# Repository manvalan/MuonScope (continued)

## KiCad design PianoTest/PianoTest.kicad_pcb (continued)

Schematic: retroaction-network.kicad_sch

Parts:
C201, C232: 1pF C0G; C_0603_1608Metric
C231: 0.5pF C0G; C_0603_1608Metric
C233: 2.2pF C0G; C_0603_1608Metric
C234: 4.7pF C0G; C_0603_1608Metric
C236, C246: 10nF C0G; C_0603_1608Metric
C241: 10pF C0G; C_0603_1608Metric
C242: 22pF C0G; C_0603_1608Metric
C243: 47pF C0G; C_0603_1608Metric
C244: 100pF C0G; C_0603_1608Metric
C270, C271, C272, C273, C274, C275: 100nF; C_0603_1608Metric
C276: 1uF; C_0603_1608Metric
R201: 100M; R_0805_2012Metric; MPN HVC0805T1006FET
R211, R251, R252, R253, R254, R255, R256, R270: 10k; R_0603_1608Metric
R212: 47k; R_0603_1608Metric
R213, R221, R222, R223, R224, R225, R226, R227, R228: 100k; R_0603_1608Metric
R214: 470k; R_0603_1608Metric
R215: 1M; R_0603_1608Metric
R216: 2.2M; R_0603_1608Metric
R217: 4.7M; R_0603_1608Metric
R218: 10M; R_0603_1608Metric
R231, R232, R233, R234, R236, R241, R242, R243, R244, R246: 100M; R_0805_2012Metric
R261, R262, R263, R264, R265, R266: 22k; R_0603_1608Metric
TP201: MCP_RST; TestPoint_Pad_D1.0mm
U201: MCP23S17-E/ML; QFN-28-1EP_6x6mm_P0.65mm_EP4.25x4.25mm; MPN MCP23S17-E/ML
U202, U203: TMUX1112RSVR; RSV0016A-MFG; MPN TMUX1112RSVR
U204, U205: BGSA142GN12; PG-TSNP-12-1; MPN BGSA142GN12E6327XTSA1

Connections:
+3V3: C271.1, C274.1, C275.1, C276.1, R270.1, U201.5 (VDD), U204.4 (VDD), U205.4 (VDD); also elsewhere on the board
+5V: C272.1, C273.1, U202.11 (VDD), U203.11 (VDD); also elsewhere on the board
/RetroactionNetwork/CFA1: C231.2, R231.1, U204.1 (RF1)
/RetroactionNetwork/CFA2: C232.2, R232.1, U204.2 (RF2)
/RetroactionNetwork/CFA3: C233.2, R233.1, U204.10 (RF3)
/RetroactionNetwork/CFA4: C234.2, R234.1, U204.9 (RF4)
/RetroactionNetwork/CFA_COM: C236.1, R236.1, U204.11 (RFC1), U204.12 (RFC2)
/RetroactionNetwork/CFB1: C241.2, R241.1, U205.1 (RF1)
/RetroactionNetwork/CFB2: C242.2, R242.1, U205.2 (RF2)
/RetroactionNetwork/CFB3: C243.2, R243.1, U205.10 (RF3)
/RetroactionNetwork/CFB4: C244.2, R244.1, U205.9 (RF4)
/RetroactionNetwork/CFB_COM: C246.1, R246.1, U205.11 (RFC1), U205.12 (RFC2)
/RetroactionNetwork/CTLA0: R251.2, R261.1, U204.7 (CTL0)
/RetroactionNetwork/CTLA1: R252.2, R262.1, U204.5 (CTL1)
/RetroactionNetwork/CTLA2: R253.2, R263.1, U204.6 (CTL2)
/RetroactionNetwork/CTLB0: R254.2, R264.1, U205.7 (CTL0)
/RetroactionNetwork/CTLB1: R255.2, R265.1, U205.5 (CTL1)
/RetroactionNetwork/CTLB2: R256.2, R266.1, U205.6 (CTL2)
/RetroactionNetwork/GPA0: R251.1, U201.17 (GPA0)
/RetroactionNetwork/GPA1: R252.1, U201.18 (GPA1)
/RetroactionNetwork/GPA2: R253.1, U201.19 (GPA2)
/RetroactionNetwork/GPA3: R254.1, U201.20 (GPA3)
/RetroactionNetwork/GPA4: R255.1, U201.21 (GPA4)
/RetroactionNetwork/GPA5: R256.1, U201.22 (GPA5)
/RetroactionNetwork/MCP_RST: C270.1, R270.2, TP201.1, U201.14 (~RESET)
/RetroactionNetwork/RF_1: R211.1, U202.16 (D1)
/RetroactionNetwork/RF_2: R212.1, U202.13 (D2)
/RetroactionNetwork/RF_3: R213.1, U202.8 (D3)
/RetroactionNetwork/RF_4: R214.1, U202.5 (D4)
/RetroactionNetwork/RF_5: R215.1, U203.16 (D1)
/RetroactionNetwork/RF_6: R216.1, U203.13 (D2)
/RetroactionNetwork/RF_7: R217.1, U203.8 (D3)
/RetroactionNetwork/RF_8: R218.1, U203.5 (D4)
/RetroactionNetwork/SEL_R1: R221.1, U201.25 (GPB0), U202.15 (SEL1)
/RetroactionNetwork/SEL_R2: R222.1, U201.26 (GPB1), U202.14 (SEL2)
/RetroactionNetwork/SEL_R3: R223.1, U201.27 (GPB2), U202.7 (SEL3)
/RetroactionNetwork/SEL_R4: R224.1, U201.28 (GPB3), U202.6 (SEL4)
/RetroactionNetwork/SEL_R5: R225.1, U201.1 (GPB4), U203.15 (SEL1)
/RetroactionNetwork/SEL_R6: R226.1, U201.2 (GPB5), U203.14 (SEL2)
/RetroactionNetwork/SEL_R7: R227.1, U201.3 (GPB6), U203.7 (SEL3)
/RetroactionNetwork/SEL_R8: R228.1, U201.4 (GPB7), U203.6 (SEL4)
CSA_IN: C201.1, C231.1, C232.1, C233.1, C234.1, C241.1, C242.1, C243.1, C244.1, R201.1, U202.1 (S1), U202.4 (S4), U202.9 (S3), U202.12 (S2), U203.1 (S1), U203.4 (S4), U203.9 (S3), U203.12 (S2); also elsewhere on the board
CSA_OUT: C201.2, C236.2, C246.2, R201.2, R211.2, R212.2, R213.2, R214.2, R215.2, R216.2, R217.2, R218.2; also elsewhere on the board
CS_MCP: U201.7 (~CS); also elsewhere on the board
GND: C270.2, C271.2, C272.2, C273.2, C274.2, C275.2, C276.2, R221.2, R222.2, R223.2, R224.2, R225.2, R226.2, R227.2, R228.2, R231.2, R232.2, R233.2, R234.2, R236.2, R241.2, R242.2, R243.2, R244.2, R246.2, R261.2, R262.2, R263.2, R264.2, R265.2, R266.2, U201.6 (VSS), U201.11 (A0), U201.12 (A1), U201.13 (A2), U201.29 (EP), U202.3 (GND), U203.3 (GND), U204.3 (GND), U204.8 (GND), U205.3 (GND), U205.8 (GND); also elsewhere on the board
HIT_LATCH: U201.24 (GPA7); also elsewhere on the board
MCP_INTA: U201.16 (INTA); also elsewhere on the board
MISO_L: U201.10 (SO); also elsewhere on the board
MOSI_L: U201.9 (SI); also elsewhere on the board
PL_FAULT: U201.23 (GPA6); also elsewhere on the board
SCLK_L: U201.8 (SCK); also elsewhere on the board

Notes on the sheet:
RETROAZIONE: R201 100M sempre presente (DC definita anche con MCP in reset). Rf 10k..10M con TMUX1112 (chiuso con SEL=1, pull-down 100k = aperti al reset).
Cf: C201 1 pF fisso (default) + banchi BGSA142: -IN -> Cf -> RFx -> RFC -> 10 nF C0G -> uscita. 100M verso GND su ogni RFx e RFC. CTL tramite partitore 10k/22k (3.3 V -> 2.27 V, pull-down al reset).

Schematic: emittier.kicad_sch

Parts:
C301, C302: 100nF; C_0603_1608Metric
C303: 10uF; C_0805_2012Metric
D301: VSMY2940G; DIO_VSMY2940G; MPN VSMY2940G
J301: TRIG est.; PinHeader_1x02_P2.54mm_Vertical
Q301: BSS138; SOT-23
R301: 47k 1%; R_0603_1608Metric
R302: 47R; R_0603_1608Metric
R303, R306: 10k; R_0603_1608Metric
R304: 1k; R_0603_1608Metric
R305: 220R; R_0805_2012Metric
U301: LTC6993CS6-2; SOT95P280X100-6N; MPN LTC6993CS6-2#TRMPBF
U302: AD5245BRJZ100; SOT65P280X145-8N; MPN AD5245BRJZ100-RL7

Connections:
+3V3: C301.1, C302.1, U301.5 (V+), U302.2 (VDD); also elsewhere on the board
+5V: C303.1, R305.1; also elsewhere on the board
/EmettitoreTest/LED_A: D301.A, R305.2
/EmettitoreTest/LED_K: D301.C, Q301.3 (D)
/EmettitoreTest/LTC_OUT: R302.1, U301.6 (OUT)
/EmettitoreTest/LTC_SET: R301.2, U301.3 (SET)
/EmettitoreTest/Q_G: Q301.1 (G), R302.2, R303.1
/EmettitoreTest/RHEO_W: R301.1, U302.1 (W)
CS_Y4: R304.1; also elsewhere on the board
GND: C301.2, C302.2, C303.2, J301.2, Q301.2 (S), R303.2, R306.2, U301.2 (GND), U301.4 (DIV), U302.3 (GND), U302.6 (AD0), U302.7 (B); also elsewhere on the board
I2C_SCL: U302.4 (SCL); also elsewhere on the board
I2C_SDA: U302.5 (SDA); also elsewhere on the board
TRIG_INPULSE: J301.1, R304.2, R306.1, U301.1 (TRIG)

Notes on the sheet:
EMETTITORE: LTC6993-2 (durata con AD5245 100k reostato + 47k) -> BSS138 -> LED IR alimentato da +5V (non piu da V_BIAS).
TRIG dallo strobe CS_Y4 (accesso SPI all indirizzo 4 del piano: il fronte di salita a fine accesso avvia l impulso) o dal connettore J301. AD5245 su I2C del bus, indirizzo 0x2C (AD0 a GND).

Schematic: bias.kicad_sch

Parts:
C501, C502: 1uF/100V; C_1206_3216Metric
C503: 100nF/100V; C_1206_3216Metric
C504, C505: 470pF/100V; C_1206_3216Metric; not fitted
C506, C507, C508, C509, C510: 100nF; C_0603_1608Metric
D501: BAT54S; SOT-23; MPN BAT54S
R501: 100R; R_0805_2012Metric
R502: 10k 0.1%; R_0805_2012Metric; MPN ERA-6ARB103V
R503: 22k; R_0603_1608Metric
R504, R505: 10k; R_0603_1608Metric
TP501: DAC_OUTA; TestPoint_Pad_D1.0mm
TP502: VTH; TestPoint_Pad_D1.0mm
U501: DAC61402RHBR; VQFN32_RHB_TEX; MPN DAC61402RHBR
U502: INA239AIDGSR; VSSOP_9AIDGST_TEX; MPN INA239AIDGSR

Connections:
+3V3: C508.1, C510.1, D501.2 (K2), R504.1, U501.15 (IOVDD), U501.16 (~CLR), U501.32 (~RST), U502.6 (VS); also elsewhere on the board
+5V: C507.1, U501.30 (DVDD); also elsewhere on the board
/BiasDiodo/AVDD_DAC: C501.1, C502.1, C503.1, R501.2, U501.28 (AVDD)
/BiasDiodo/CCOMPA: C504.1, U501.7 (CCOMPA)
/BiasDiodo/CCOMPB: C505.1, U501.18 (CCOMPB)
/BiasDiodo/DAC_OUTA: C504.2, R502.1, TP501.1, U501.6 (SENSEPA), U501.8 (OUTA), U502.10 (IN+)
/BiasDiodo/DAC_OUTB: C505.2, R503.1, U501.17 (OUTB), U501.19 (SENSEPB)
/BiasDiodo/DAC_REF: C509.1, U501.26 (REFIO)
CS_DAC: U501.12 (~SYNC); also elsewhere on the board
CS_INA: U502.1 (CS); also elsewhere on the board
GND: C501.2, C502.2, C503.2, C506.2, C507.2, C508.2, C509.2, C510.2, D501.1 (A1), R505.2, U501.5 (SENSENA), U501.13 (~LDAC), U501.14 (GND), U501.20 (SENSENB), U501.25 (REFGND), U501.27 (AVSS), U501.29 (AGND), U501.33 (EP), U502.7 (GND); also elsewhere on the board
MISO_L: U501.9 (SDO), U502.4 (MISO); also elsewhere on the board
MOSI_L: U501.11 (SDIN), U502.2 (MOSI); also elsewhere on the board
PL_FAULT: R504.2, U501.31 (~FAULT), U502.3 (ALERT); also elsewhere on the board
SCLK_L: U501.10 (SCLK), U502.5 (SCLK); also elsewhere on the board
VBIAS_SH: R502.2, U502.8 (VBUS), U502.9 (IN-); also elsewhere on the board
VHV_36V: R501.1; also elsewhere on the board
VTH: C506.1, D501.3 (K1/A2), R503.2, R505.1, TP502.1; also elsewhere on the board

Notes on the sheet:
BIAS LOCALE: DAC61402 alimentato da VHV_36V (bus pin 8) con RC 100R + 2x1uF/100V. OUTA -> shunt 10k (INA239) -> VBIAS_SH -> RC 1k/100nF vicino al diodo.
INA239 con shunt 10k: ADCRANGE=1 -> 1.25 uV/LSB = 125 pA/LSB, fondo scala 4.1 uA; ADCRANGE=0 -> 500 pA/LSB, 16.4 uA. Errori: Vos 5 uV max (0.5 nA), IB 0.1 nA tip / 2.5 nA max.
DAC: AVDD ~36 V -> uscita max ~34.5 V (headroom 1.5 V). OUTB (range 0-5 V) -> partitore 22k/10k -> VTH soglia del comparatore (0-1.56 V, 0.38 mV/LSB), BAT54S di protezione. CCOMP DNP.

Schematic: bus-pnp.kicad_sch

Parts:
C401, C402, C403, C404, C405, C406, C407, C408, C416, C417: 100nF; C_0603_1608Metric
C409, C410: 10uF; C_0805_2012Metric
C411, C412: 100nF/100V; C_1206_3216Metric
C413, C414: 1uF; C_0603_1608Metric
C415: 27pF C0G; C_0603_1608Metric
D401, D402, D403, D404, D405, D406, D407, D408, D409, D410, D411, D412, D413, D414, D415, D416, D417, D418, D419, D420: TPD1E10B06; D_0402_1005Metric; MPN TPD1E10B06DPYR
J401: J_IN MAIN; FPC-05F-28PH20; MPN FPC-05F-28PH20
J402: J_OUT MAIN; FPC-05F-28PH20; MPN FPC-05F-28PH20
R401: 0R; R_0603_1608Metric
R402, R403, R404, R405, R406: 100k; R_0603_1608Metric
R407: 2k; R_0603_1608Metric
TP401: CS_Y3; TestPoint_Pad_D1.0mm
TP402: CS_Y4; TestPoint_Pad_D1.0mm
TP403: CS_Y5; TestPoint_Pad_D1.0mm
U401: 74HC283; TSSOP-16_4.4x5mm_P0.65mm; MPN 74HC283PW
U402: 74HC85; TSSOP-16_4.4x5mm_P0.65mm; MPN 74HC85PW
U403: 74HC138; TSSOP-16_4.4x5mm_P0.65mm; MPN 74HC138PW
U404: SN74LVC2G17DBVR; SOT-23-6; MPN SN74LVC2G17DBVR
U405: SN74LVC1G125DBVR; SOT-23-5; MPN SN74LVC1G125DBVR
U406: SN74LVC1G332DBVR; SOT-23-6; MPN SN74LVC1G332DBVR
U407: SN74LVC1G07DBVR; SOT-23-5; MPN SN74LVC1G07DBVR
U408: 25AA02E48T-I/SN; SOIC-8_3.9x4.9mm_P1.27mm; MPN 25AA02E48T-I/SN
U409: SN74LVC1G123DCUR; VSSOP-8_2.3x2mm_P0.5mm; MPN SN74LVC1G123DCUR
U410: SN74LVC1G06DBVR; SOT-23-5; MPN SN74LVC1G06DBVR

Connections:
1V25_REF: C414.1, J401.6, J402.6; also elsewhere on the board
2V5_REF: C413.1, J401.5, J402.5; also elsewhere on the board
+3V3: C401.1, C402.1, C403.1, C404.1, C405.1, C406.1, C407.1, C408.1, C409.1, C416.1, C417.1, J401.3, J402.3, R402.1, R407.1, U401.7 (CIN), U401.16 (VCC), U402.3 (IA=B), U402.16 (VCC), U403.16 (VCC), U404.5 (VCC), U405.5 (VCC), U406.5 (VCC), U407.5 (VCC), U408.3 (~WP), U408.7 (~HOLD), U408.8 (VCC), U409.3 (~CLR), U409.8 (VCC), U410.5 (VCC); also elsewhere on the board
+5V: C410.1, J401.2, J402.2; also elsewhere on the board
/bus-pnp/AGTB: U402.5 (QA>B), U406.3 (B)
/bus-pnp/ALTB: U402.7 (QA<B), U406.6 (C)
/bus-pnp/BUS_ADDR0: D407.1 (A1), J401.18, J402.18, U403.1 (A0)
/bus-pnp/BUS_ADDR1: D408.1 (A1), J401.19, J402.19, U403.2 (A1)
/bus-pnp/BUS_ADDR2: D409.1 (A1), J401.20, J402.20, U403.3 (A2)
/bus-pnp/BUS_ALERT_N: D413.1 (A1), J401.24, J402.24, U407.4 (Y)
/bus-pnp/BUS_CS_MASTER: D406.1 (A1), J401.17, J402.17, R402.2, U403.4 (~E1), U406.1 (A)
/bus-pnp/BUS_HIT_N: D414.1 (A1), J401.28, J402.28, U410.4 (Y)
/bus-pnp/BUS_MISO: D403.1 (A1), J401.13, J402.13, U405.4 (Y)
/bus-pnp/BUS_MOSI: D402.1 (A1), J401.12, J402.12, U404.3 (2A)
/bus-pnp/BUS_PREFIX0: D410.1 (A1), J401.21, J402.21, U402.10 (A0)
/bus-pnp/BUS_PREFIX1: D411.1 (A1), J401.22, J402.22, U402.12 (A1)
/bus-pnp/BUS_PREFIX2: D412.1 (A1), J401.23, J402.23, U402.13 (A2)
/bus-pnp/BUS_SCLK: D401.1 (A1), J401.11, J402.11, U404.1 (1A)
/bus-pnp/CS_EEP: U403.9 (~Y6), U408.1 (~CS)
/bus-pnp/CS_Y5: TP403.1, U403.10 (~Y5)
/bus-pnp/GND_A: J401.7, J402.7, R401.1
/bus-pnp/HIT_PULSE: U409.5 (Q), U410.2 (A)
/bus-pnp/ID_IN0: D415.1 (A1), J401.25, R404.1, U401.5 (A1), U402.9 (B0)
/bus-pnp/ID_IN1: D416.1 (A1), J401.26, R405.1, U401.3 (A2), U402.11 (B1)
/bus-pnp/ID_IN2: D417.1 (A1), J401.27, R406.1, U401.14 (A3), U402.14 (B2)
/bus-pnp/ID_OUT0: D418.1 (A1), J402.25, U401.4 (S1)
/bus-pnp/ID_OUT1: D419.1 (A1), J402.26, U401.1 (S2)
/bus-pnp/ID_OUT2: D420.1 (A1), J402.27, U401.13 (S3)
/bus-pnp/MISO_OE_N: U405.1 (~OE), U406.4 (Y)
/bus-pnp/MONO_C: C415.2, U409.6 (Cext)
/bus-pnp/MONO_RC: C415.1, R407.2, U409.7 (Rext/Cext)
/bus-pnp/PL_SEL: U402.6 (QA=B), U403.6 (E3)
CS_ADC: U403.15 (~Y0); also elsewhere on the board
CS_DAC: U403.14 (~Y1); also elsewhere on the board
CS_INA: U403.13 (~Y2); also elsewhere on the board
CS_MCP: U403.7 (~Y7); also elsewhere on the board
CS_Y3: TP401.1, U403.12 (~Y3); also elsewhere on the board
CS_Y4: TP402.1, U403.11 (~Y4); also elsewhere on the board
GND: C401.2, C402.2, C403.2, C404.2, C405.2, C406.2, C407.2, C408.2, C409.2, C410.2, C411.2, C412.2, C413.2, C414.2, C416.2, C417.2, D401.2 (A2), D402.2 (A2), D403.2 (A2), D404.2 (A2), D405.2 (A2), D406.2 (A2), D407.2 (A2), D408.2 (A2), D409.2 (A2), D410.2 (A2), D411.2 (A2), D412.2 (A2), D413.2 (A2), D414.2 (A2), D415.2 (A2), D416.2 (A2), D417.2 (A2), D418.2 (A2), D419.2 (A2), D420.2 (A2), J401.1, J401.4, J401.10, J401.16, J401.MP (MountPin), J402.1, J402.4, J402.10, J402.16, J402.MP (MountPin), R401.2, R403.2, R404.2, R405.2, R406.2, U401.2 (B2), U401.6 (B1), U401.8 (GND), U401.11 (B4), U401.12 (A4), U401.15 (B3), U402.1 (B3), U402.2 (IA<B), U402.4 (IA>B), U402.8 (GND), U402.15 (A3), U403.5 (~E2), U403.8 (GND), U404.2 (GND), U405.3 (GND), U406.2 (GND), U407.3 (GND), U408.4 (VSS), U409.1 (~A), U409.4 (GND), U410.3 (GND); also elsewhere on the board
HIT: U409.2 (B); also elsewhere on the board
I2C_SCL: D405.1 (A1), J401.15, J402.15; also elsewhere on the board
I2C_SDA: D404.1 (A1), J401.14, J402.14; also elsewhere on the board
MCP_INTA: U407.2 (A); also elsewhere on the board
MISO_L: R403.1, U405.2 (A), U408.2 (SO); also elsewhere on the board
MOSI_L: U404.4 (2Y), U408.5 (SI); also elsewhere on the board
SCLK_L: U404.6 (1Y), U408.6 (SCK); also elsewhere on the board
VHV_36V: C411.1, J401.8, J402.8; also elsewhere on the board
VHV_36V_2: C412.1, J401.9, J402.9

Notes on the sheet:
BUS MIKILAB REV5.0 - MAIN 28 pin. J_IN dal piano precedente, J_OUT verso il successivo: tutto passante tranne ID (25-27), che esce come ID+1 (74HC283).
Piano selezionato se PREFIX = ID_IN (74HC85 QA=B -> E3 del 138). CS_MASTER su ~E1, ~E2 a GND. Y0 ADC, Y1 DAC, Y2 INA, Y3-Y5 test point, Y6 EEPROM ID, Y7 MCP23S17.
MISO verso il bus tramite 74LVC1G125, abilitato solo con piano selezionato e CS_MASTER basso. ALERT# open-drain (74LVC1G07) da INTA (MCP con MIRROR=1). Pull-up I2C e ALERT# sulla scheda master.
REV5.1: pin 28 = HIT# (open-drain, attivo basso, pull-up 4.7k sul master). HIT del comparatore -> monostabile 74LVC1G123 (2k + 27 pF, ~170-200 ns) -> 74LVC1G06 open-drain. Passante J_IN -> J_OUT.
FPC: XUNPU FPC-05F-28PH20 (LCSC C2856807), footprint PianoTest:FPC-05F-28PH20 importato da EasyEDA. Contatti in basso.

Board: 4 copper layers, 230 parts (0 on the bottom side), 134 nets, no tracks yet.

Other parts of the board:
H1, H2, H3, H4: MountingHole_3.2mm_M3

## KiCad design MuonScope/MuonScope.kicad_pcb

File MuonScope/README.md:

# MuonScope

Progetto KiCad 10 originale del rivelatore MuonScope (scheda di comando ESP32, modulo Power, rivelatore, rete di retroazione, emettitore di test), con le correzioni della revisione del 2026-10-14. Schema esportato in `MuonScope-schema.pdf`. La specifica del bus è in `docs/mikilab_bus_protocol.md` (BPS-MIKILAB-2026-REV5.0).

I fogli del rivelatore, della retroazione e dell'emettitore sono superati dal progetto `../PianoTest`. Qui contano soprattutto il modulo Power e la scheda di comando.

## Modulo Power (revisione 2026-10-14)

- **Boost LT8330:** collegamenti di SW, diodo e FBX corretti. Uscita fissa 36,1 V (R19 1M, R20 46,4k), L6 XFL4020-103MEC, condensatori da 100 V.
- **Uscita VHV_36V:** F2 100 mA/63 V, poi Q5 Si2309CDS (−60 V) comandato da VBIAS_ENABLE tramite Q6 BSS138, con D5 da 12 V sul gate, poi RC 10 Ω + 2×2,2 µF/100 V. R39 da 100k scarica l'uscita: a boost spento l'uscita va a 0 V.
- **Bus:** VHV_36V arriva ai pin V_BIAS_1/V_BIAS_2 attraverso R32/R33 10 Ω e C53/C54 100 nF C0G. Il pinout del connettore non cambia.
- **DAC61402, INA239 e contorno:** non montati (DNP), perché la regolazione del bias e la misura di corrente sono sul piano. SPI_DAC_CS, SPI_INA239A/B_CS e DAC61402_FAULT sul BUS_POWER restano non collegati.
- **VREF_ENABLE:** attivo alto. Pull-up a 5 V e comando con BSS138 (Q3), R31 100k: a riposo i riferimenti sono spenti.
- **Jack J1:** centro = +VIN. Aggiunti F1 PTC, Q4 P-MOS contro l'inversione di polarità e D4 SMAJ15A.
- **Net class:** V_Bias_36V per l'alta tensione. Regola di clearance per gli FPC a 0,5 mm in `MuonScope.kicad_dru`.

## Altre correzioni

- **Retroazione:** SI e SO dell'MCP23S17 corretti, MPN di C18.
- **Emettitore:** SDA e SCL dell'AD5245 corretti, SET dell'LTC6993 con reostato + 47k, R25 collegata al gate di Q1.
- **Rivelatore:** C1 da 100 V, secondo canale dell'OPA come inseguitore. Il simbolo dell'OPA4172 ha ancora il pinout del duale: è corretto solo nel PianoTest.
- **Comando:** pin 5V dell'ESP32 portato su +5V (prima era su 2V5_REF).

## Stato

- **ERC:** 93 violazioni. Sono soprattutto pin dell'ESP32 non usati e i segnali del modulo Power non esportati dal foglio di comando.
- **PCB:** layout precedente, non aggiornato con queste modifiche.
- **Footprint:** quelli `MIKILAB_*` vengono dalla libreria esterna MIKILAB (variabile `${MIKILAB}`), non inclusa nel repository.

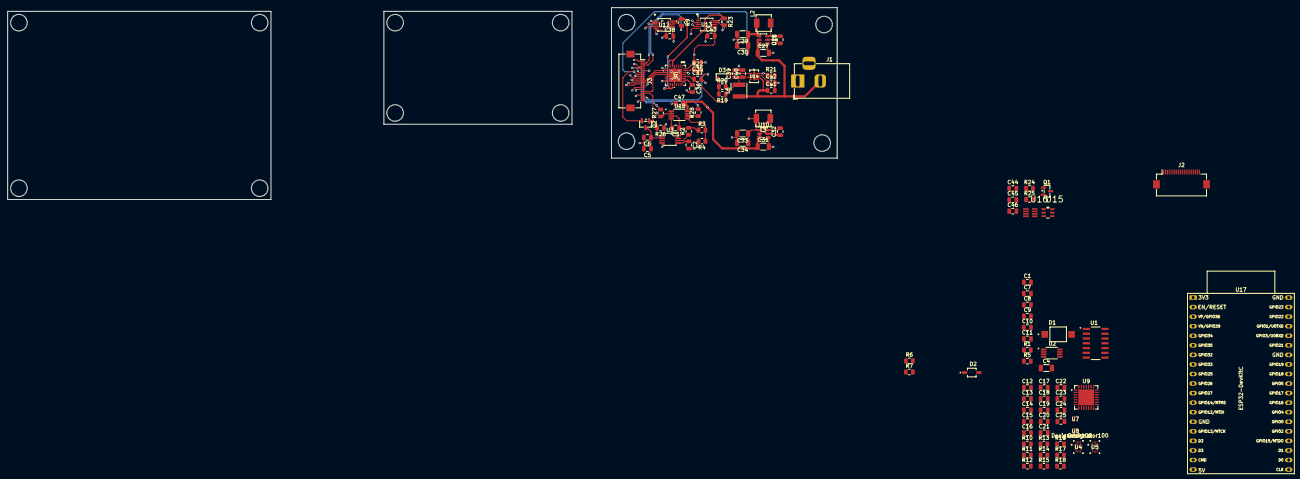
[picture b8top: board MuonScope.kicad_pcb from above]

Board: 4 copper layers, 220.5 x 51.0 mm, 102 parts (0 on the bottom side), 90 nets.

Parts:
C1, C5, C8, C10, C20, C21, C22, C23, C24, C28, C32, C35, C37, C38, C43, C44, C45, C47: 100nF; C_0805_2012Metric
C2, C3, C6, C7, C9, C11, C25, C42, C46: 1uF; C_0805_2012Metric
C4: 47uF; C_1206_3216Metric
C12: 15pF; C_0805_2012Metric
C13: 22pF; C_0805_2012Metric
C14: 47pF; C_0805_2012Metric
C15: 100 pF; C_0805_2012Metric
C16: 1pF; C_0805_2012Metric
C17: 2.2pF; C_0805_2012Metric
C18: 4.7pF; C_0805_2012Metric
C19: 10pF; C_0805_2012Metric
C27, C29, C30, C31, C33, C34: 22uF; C_1206_3216Metric
C36: 220nF; C_0805_2012Metric
C39, C40, C41: 4.7uF; C_0805_2012Metric
D1: VBPW34S; XDCR_VBPW34S
D2: VSMY2940G; DIO_VSMY2940G
D3: PMEG6010CEJ; D_SOD-323F
J1: Barrel_Jack; BarrelJack_Horizontal
J2: Conn_01x20_Socket; Hirose_FH12-20S-0.5SH_1x20-1MP_P0.50mm_Horizontal
J3: Conn_01x22_Socket; Hirose_FH12-22S-0.5SH_1x22-1MP_P0.50mm_Horizontal
L2, L3: 3.3uH; L_Changjiang_FXL0420
L6: 10uH; L_Wurth_WE-LQSH-4020
Q1: BSS138; SOT-23
Q2: BSS84; SOT-23
R1, R11, R19: 1M; R_0805_2012Metric
R2, R9, R23: 1; R_0805_2012Metric
R3, R4, R18, R21, R24, R25, R26: 10K; R_0805_2012Metric
R5, R6: 47; R_0805_2012Metric
R7: 2.2k; R_0805_2012Metric
R10: 2.2M; R_0805_2012Metric
R12: 470k; R_0805_2012Metric
R13: 220k; R_0805_2012Metric
R14: 100k; R_0805_2012Metric
R15: 47k; R_0805_2012Metric
R16: 22k; R_0805_2012Metric
R17: 10k; R_0805_2012Metric
R20, R22: 52.3k; R_0805_2012Metric
R27, R28: 10; R_0805_2012Metric
U1: OPA4172ID; SOIC127P600X175-14N
U2: ADS8326IDGKT; SOP65P490X110-8N
U3: REF5025IDGK; MSOP-8_3x3mm_P0.65mm
U4, U5: TMUX1112RSVR; RSV0016A-MFG
U6: DAC61402RHBR; VQFN32_RHB_TEX
U7, U8: BGSA142GN12; PG-TSNP-12-1
U9: MCP23S17_ML; QFN-28-1EP_6x6mm_P0.65mm_EP4.25x4.25mm
U10: AP63203WU; TSOT-23-6
U11: AP63205WU; TSOT-23-6
U12, U13: INA239AIDGSR; VSSOP_9AIDGST_TEX
U14: LT8330HDDB_TRPBF; DFN-8_DDB
U15: LTC6993CS6-2TRMPBF; SOT95P280X100-6N
U16: AD5245BRJZ10-RL7; SOT65P280X145-8N
U17: ESP32-DevKitC
U18: OPA2172IDGKR; OPA2172IDGKR_SOP65P490X110-8N

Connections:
+2V5: C4.1, U2.1 (REF)
+3.3V: C9.1, C10.1, C20.2, C21.2, C22.2, C23.2, C24.2, C25.1, C33.1, C34.1, C35.2, C38.2, C43.2, C44.2, C45.2, J2.3, J3.9, L3.2, R18.1, R22.2, R26.1, U2.8 (VDD), U4.11 (VDD), U5.11 (VDD), U6.15 (IOVDD), U6.16 (*CLR), U6.30 (DVDD), U6.32 (*RST), U7.4 (VDD), U8.4 (VDD), U9.5 (VDD), U10.1 (FB), U12.6 (VS), U13.6 (VS), U15.5 (V+), U16.2 (VDD), U16.8 (A)
+5V: C7.1, C8.1, C29.1, C30.1, C31.1, C47.2, J2.2, J3.8, L2.2, Q2.2 (S), U1.8 (V+), U10.2 (EN), U10.3 (IN), U11.1 (FB), U18.8
/CommandPCB/2V5_REF: J2.5, U17.19 (5V)
/CommandPCB/I2C_SCL: J2.15, U17.36 (GPIO22)
/CommandPCB/I2C_SDA: J2.14, U17.33 (GPIO21)
/CommandPCB/RET_RESET: J2.20, U17.10 (DAC_2/ADC2_CH9/GPIO26)
/CommandPCB/SPI_ADS8326_CS: J2.16, U17.9 (DAC_1/ADC2_CH8/GPIO25)
/CommandPCB/SPI_MISO: J2.13, U17.31 (GPIO19)
/CommandPCB/SPI_MOSI: J2.12, U17.37 (GPIO23)
/CommandPCB/SPI_RET_CS: J2.17, U17.8 (32K_XN/GPIO33/ADC1_CH5)
/CommandPCB/SPI_SCLK: J2.11, U17.30 (GPIO18)
/CommandPCB/TRIG_INPULSE: J2.19, U17.13 (MTDI/GPIO12/ADC2_CH5)
/EmettitoreTest/I2C_SDA: R24.2, U15.1 (TRIG), U16.4 (SCL)
/EmettitoreTest/V_BIAS: C46.1, R7.1
/Power Module/1V25_REF: J3.6, R28.2
/Power Module/2V5_REF: J3.5, R27.2
/Power Module/36V: C37.1, C39.1, C40.1, L6.2, R19.1, U6.28 (AVDD), U14.3 (SW_2), U14.4 (SW)
/Power Module/DAC61402_FAULT: J3.20, R22.1, U6.31 (*FAULT)
/Power Module/OUT1: R23.1, U6.6 (SENSEPA), U6.8 (OUTA), U13.8 (VBUS), U13.10 (IN+)
/Power Module/OUT2: R9.1, U6.17 (OUTB), U6.19 (SENSEPB), U12.8 (VBUS), U12.10 (IN+)
/Power Module/SPI_DAC_CS: J3.17, U6.12 (*SYNC)
/Power Module/SPI_INA239A_CS: J3.15, U12.1 (CS)
/Power Module/SPI_INA239B_CS: J3.16, U13.1 (CS)
/Power Module/SPI_MISO: J3.13, U6.9 (SDO), U12.4 (MISO), U13.4 (MISO)
/Power Module/SPI_MOSI: J3.12, U6.11 (SDIN), U12.2 (MOSI), U13.2 (MOSI)
/Power Module/SPI_SCLK: J3.11, U6.10 (SCLK), U12.5 (SCLK), U13.5 (SCLK)
/Power Module/VBIAS_ENABLE: J3.19, R21.1, U14.8 (EN/UVLO)
/Power Module/VIN: C27.1, C41.1, J1.2, L6.1, U11.2 (EN), U11.3 (IN), U14.6 (VIN)
/Power Module/VREF_ENABLE: J3.18, Q2.1 (G), R26.2
/Power Module/V_BIAS_1: J3.2, R23.2, U13.9 (IN-)
/Power Module/V_BIAS_2: J3.3, R9.2, U12.9 (IN-)
/Rivelatore/CSA_OUT: C11.1, R5.2, U2.2 (+IN)
/Rivelatore/RET_RESET: R18.2, U9.14 (~RESET)
/Rivelatore/RetroactionNetwork/C_BYPASS_IN: D1.A, U1.2 (-INA), U4.1 (S1), U4.4 (S4), U4.9 (S3), U4.12 (S2), U5.1 (S1), U5.4 (S4), U5.9 (S3), U5.12 (S2), U7.11 (RFC1), U7.12 (RFC2), U8.11 (RFC1), U8.12 (RFC2)
/Rivelatore/RetroactionNetwork/C_BYPASS_OUT: C12.2, C13.2, C14.2, C15.2, C16.2, C17.2, C18.2, C19.2, R5.1, R10.2, R11.2, R12.2, R13.2, R14.2, R15.2, R16.2, R17.2, U1.1 (OUTA)
/Rivelatore/SPI_MISO: U2.6 (DOUT), U9.9 (SI)
/Rivelatore/SPI_SCLK: U2.7 (DCLOCK), U9.8 (SCK)
GND: C1.2, C2.2, C3.2, C4.2, C5.2, C6.2, C7.2, C8.2, C9.2, C10.2, C11.2, C20.1, C21.1, C22.1, C23.1, C24.1, C25.2, C27.2, C29.2, C30.2, C31.2, C33.2, C34.2, C35.1, C36.2, C37.2, C38.1, C39.2, C40.2, C41.2, C42.2, C43.1, C44.1, C45.1, C46.2, C47.1, J1.1, J2.1, J2.4, J2.7, J2.10, J2.18, J3.1, J3.4, J3.7, J3.10, J3.14, J3.21, J3.22, Q1.2 (S), R4.2, R20.2, R21.2, R24.1, R25.1, U1.4 (V-), U2.3 (-IN), U2.4 (GND), U3.4 (GND), U4.3 (GND), U5.3 (GND), U6.5 (SENSENA), U6.13 (*LDAC), U6.14 (GND), U6.20 (SENSENB), U6.25 (REFGND), U6.27 (AVSS), U6.29 (AGND), U6.33 (GND), U7.3 (GND), U7.8 (GND), U8.3 (GND), U8.8 (GND), U9.6 (VSS), U9.11 (A0), U9.12 (A1), U9.13 (A2), U9.29 (EP), U10.4 (GND), U11.4 (GND), U12.7 (GND), U13.7 (GND), U14.5 (GND), U14.9 (EPAD), U15.2 (GND), U15.4 (DIV), U16.3 (GND), U16.6 (AD0), U16.7 (B), U17.14 (GND), U17.32 (GND), U17.38 (GND), U18.4
unnamed: C1.1, D1.K, R1.2
unnamed: C3.1, R2.2, R3.1, U18.3
unnamed: D2.A, R7.2
unnamed: D3.2 (A), U14.1 (FBX)
unnamed: D3.1 (K), R19.2, R20.1
unnamed: D2.C, Q1.3 (D)
unnamed: Q1.1 (G), R6.2
unnamed: C5.1, C6.1, Q2.3 (D), U3.2 (Vin)
unnamed: R3.2, R4.1, U18.5
unnamed: R27.1, U18.1, U18.2
unnamed: R28.1, U18.6, U18.7
unnamed: C2.1, U3.5 (Trim/NR)
unnamed: R2.1, U3.6 (Vout)
unnamed: R17.1, U4.16 (D1)
unnamed: R16.1, U4.13 (D2)
unnamed: R15.1, U4.8 (D3)
unnamed: R14.1, U4.5 (D4)
unnamed: U4.15 (SEL1), U9.25 (GPB0)
unnamed: U4.14 (SEL2), U9.26 (GPB1)
unnamed: U4.7 (SEL3), U9.27 (GPB2)
unnamed: U4.6 (SEL4), U9.28 (GPB3)
unnamed: R13.1, U5.16 (D1)
unnamed: R12.1, U5.13 (D2)
unnamed: R11.1, U5.8 (D3)
unnamed: R10.1, U5.5 (D4)
unnamed: U5.15 (SEL1), U9.1 (GPB4)
unnamed: U5.14 (SEL2), U9.2 (GPB5)
unnamed: U5.7 (SEL3), U9.3 (GPB6)
unnamed: U5.6 (SEL4), U9.4 (GPB7)
unnamed: C36.1, U6.26 (REFIO)
unnamed: U7.7 (CTL0), U9.20 (GPA3)
unnamed: U7.5 (CTL1), U9.21 (GPA4)
unnamed: U7.6 (CTL2), U9.22 (GPA5)
unnamed: C12.1, U7.1 (RF1)
unnamed: C13.1, U7.2 (RF2)
unnamed: C14.1, U7.10 (RF3)
unnamed: C15.1, U7.9 (RF4)
unnamed: U8.7 (CTL0), U9.17 (GPA0)
unnamed: U8.5 (CTL1), U9.18 (GPA1)
unnamed: U8.6 (CTL2), U9.19 (GPA2)
unnamed: C16.1, U8.1 (RF1)
unnamed: C17.1, U8.2 (RF2)
unnamed: C18.1, U8.10 (RF3)
unnamed: C19.1, U8.9 (RF4)
unnamed: C32.2, U10.6 (BST)
unnamed: C32.1, L3.1, U10.5 (SW)
unnamed: C28.2, U11.6 (BST)
unnamed: C28.1, L2.1, U11.5 (SW)
unnamed: C42.1, U14.7 (INTVCC)
unnamed: R6.1, U15.6 (OUT)
unnamed: U15.3 (SET), U16.1 (W)
